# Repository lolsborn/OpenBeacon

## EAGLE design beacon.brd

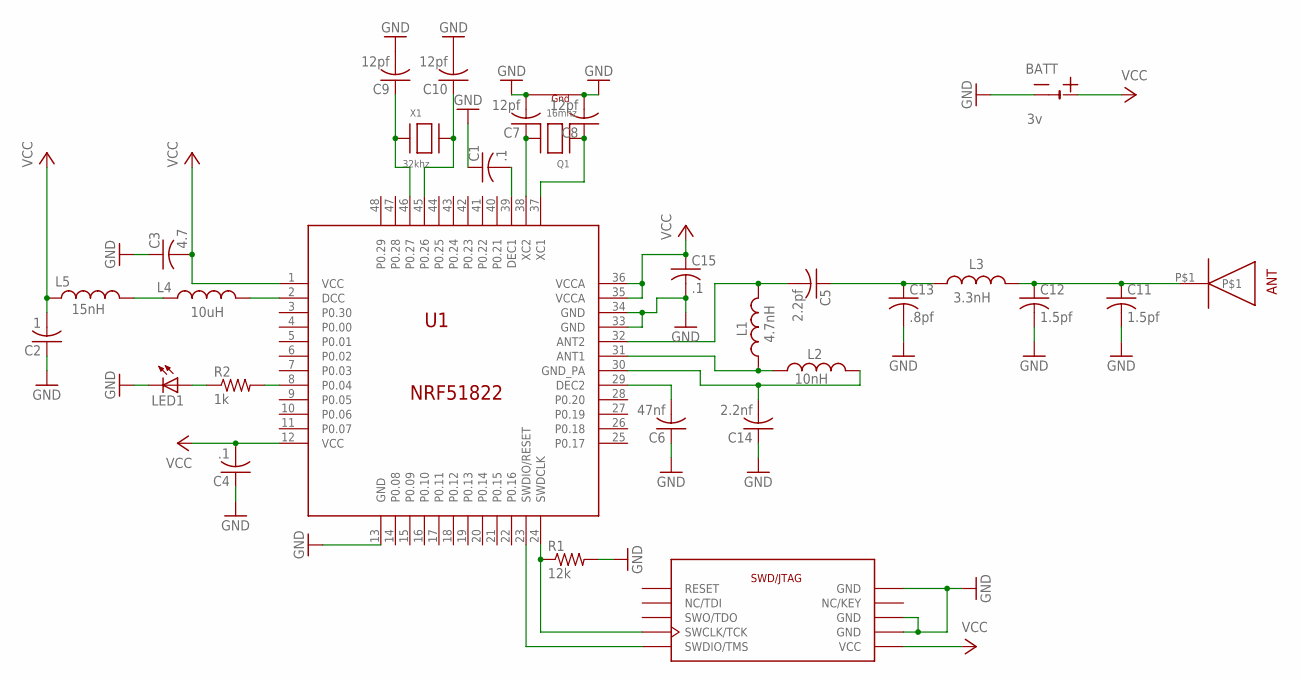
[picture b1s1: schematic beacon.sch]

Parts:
BATT: 3v; CR2032-SMD
C1, C4, C15: .1; C0603
C2: 1; C0603
C3: 4.7; C0603; MOUSER 80-C0603C475K8P
C5: 2.2pf; C0603; DIGIKEY 1276-1084-1-ND
C6: 47nf; C0603; MOUSER 81-GRM188R71H473KA61
C7, C8, C9, C10: 12pf; C0603; MOUSER 603-CC603JRNPO9BN120
C11, C12: 1.5pf; C0603; MOUSER 77-VJ0603A1R5BXJPBC
C13: .8pf; C0603; MOUSER 81-GJM1555C1HR80WB1D
C14: 2.2nf; C0603; DIGIKEY 399-1085-1-ND
L1: 4.7nH; 0603; DIGIKEY 587-1541-1-ND
L2: 10nH; 0603; MOUSER 871-B82496C3100J
L3: 3.3nH; 0603; MOUSER 609-L-14C3N3SV4T
L4: 10uH; 0603; MOUSER 963-LK1608100K-T
L5: 15nH; 0603; MOUSER 871-B82496C3150J
LED1: LEDCHIP-LED0603; CHIP-LED0603
Q1: 16mhz; NX3225; DIGIKEY 535-10267-1-ND
R1: 12k; R0603; DIGIKEY RMCF0603JT12K0CT-ND
R2: 1k; R0603
U1: NRF51822; QFN40P600X600X100-49N
U$1: SWD_HEADERSWD_SMT; SWD_SMT
U$2: BLE_ANT
X1: 32khz; XTAL3215; MOUSER 815-ABS07-32.768KHZT

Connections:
GND: BATT.-, C1.1, C2.1, C3.1, C4.1, C6.1, C7.2, C8.2, C9.2, C10.2, C11.2, C12.2, C13.2, C14.1, C15.2, LED1.C, Q1.2 (G2), Q1.4 (G1), R1.2, U1.13 (GND), U1.33 (GND), U1.34 (GND), U$1.P3 (GND), U$1.P5 (GND), U$1.P9 (GND)
unnamed: C1.2, U1.39 (DEC1)
unnamed: C6.2, U1.29 (DEC2)
unnamed: C7.1, Q1.3 (X2), U1.38 (XC2)
unnamed: C8.1, Q1.1 (X1), U1.37 (XC1)
unnamed: C9.1, U1.46 (P0.27), X1.P$1
unnamed: C10.1, U1.45 (P0.26), X1.P$2
unnamed: C11.1, C12.1, L3.2, U$2.P$1
unnamed: LED1.A, R2.1
unnamed: R2.2, U1.8 (P0.04)
unnamed: L4.2, U1.2 (DCC)
unnamed: L4.1, L5.2
unnamed: L1.1, L2.1, U1.31 (ANT1)
unnamed: C14.2, L2.2, U1.30 (GND_PA)
unnamed: C5.2, L1.2, U1.32 (ANT2)
unnamed: C5.1, C13.1, L3.1
SWDCLK: R1.1, U1.24 (SWDCLK), U$1.P4 (SWCLK/TCK)
SWDIO: U1.23 (SWDIO/RESET), U$1.P2 (SWDIO/TMS)
VCC: BATT.+$1 (+1), BATT.+$2 (+1), C2.2, C3.2, C4.2, C15.1, L5.1, U1.1 (VCC), U1.12 (VCC), U1.35 (VCCA), U1.36 (VCCA), U$1.P1 (VCC)

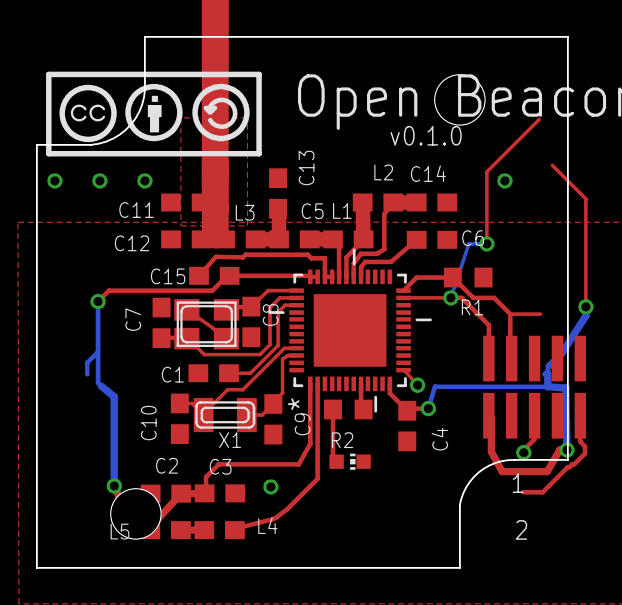
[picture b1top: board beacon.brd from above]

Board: 2 copper layers, 29.5 x 29.5 mm, 31 parts (1 on the bottom side), 19 nets.

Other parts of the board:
U$3: LOGO_CC-BY-SA
U$4: OSHWLOGO_TOL_0.2

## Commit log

2014-04-18 initial
